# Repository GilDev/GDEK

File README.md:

# GDEK: Your first ergonomic keyboard

Want to try ergonomic keyboards? Don’t know where to start? Don’t want to break the bank yet before knowing what you really want? This may be the keyboard for you.

I created this keyboard following [a little crowdfunding campaign](https://fr.ulule.com/clavier-ergonomique-gildev/) I ran for people that were interested in improving their typing comfort but didn’t want to spend too much money on a device they might not like or would like some feature. This keyboard was entirely designed from scratch, after experimenting for some years with a TypeMatrix 2030, a original X-Bows (Kickstarter edition) and a personnal variant of the Sofle Choc RGB.

## Features

* **4×6 matrix**: you don’t risk missing anything, you can always disable things later on in software to see if missing that top number row would work for you. You can even type in [Bépo](https://bepo.fr/) with minimal modifications!
* **Split**: optimal hands placement, with room in the middle for a trackball or Magic Trackpad, and a simple audio cable to connect the two halves with connectors that won’t mechanically constrain your cable
* **Compact**: despite the “full” matrix, it’s easy to bring it along
* **5 keys thumb cluster**: enough for anything you could imagine
* **Supports MX, Kailh Choc and Gateron KS-33 low-profile switches**: I personnaly use KS-33 switches as they’re low-profile, cheap and support standard MX-compatible keycaps
* **Per-key RGB**: more than just for looks, they can indicate what some keys do, which layer you’re on, etc.
* **Encoder**: you may think it’s a gimmick, but at least you can try it and see if you like it. I love it to scroll, move the cursor, control volume, etc.
* **RP2040**: a very cool and powerful microcontroller that will support any features you could image without breaking a sweat. Easy to flash: it appears like a USB drive that you can drag the firmware onto
* **QMK firmware with VIA support**: easily configurable and customizable via a web app
* **Assembly-friendly**: send the PCB to be assembled and just solder the switches, encoders and audio TRS jack (pretty easy)
* **Open-source**: you can modify the design to your liking, design a case and so on

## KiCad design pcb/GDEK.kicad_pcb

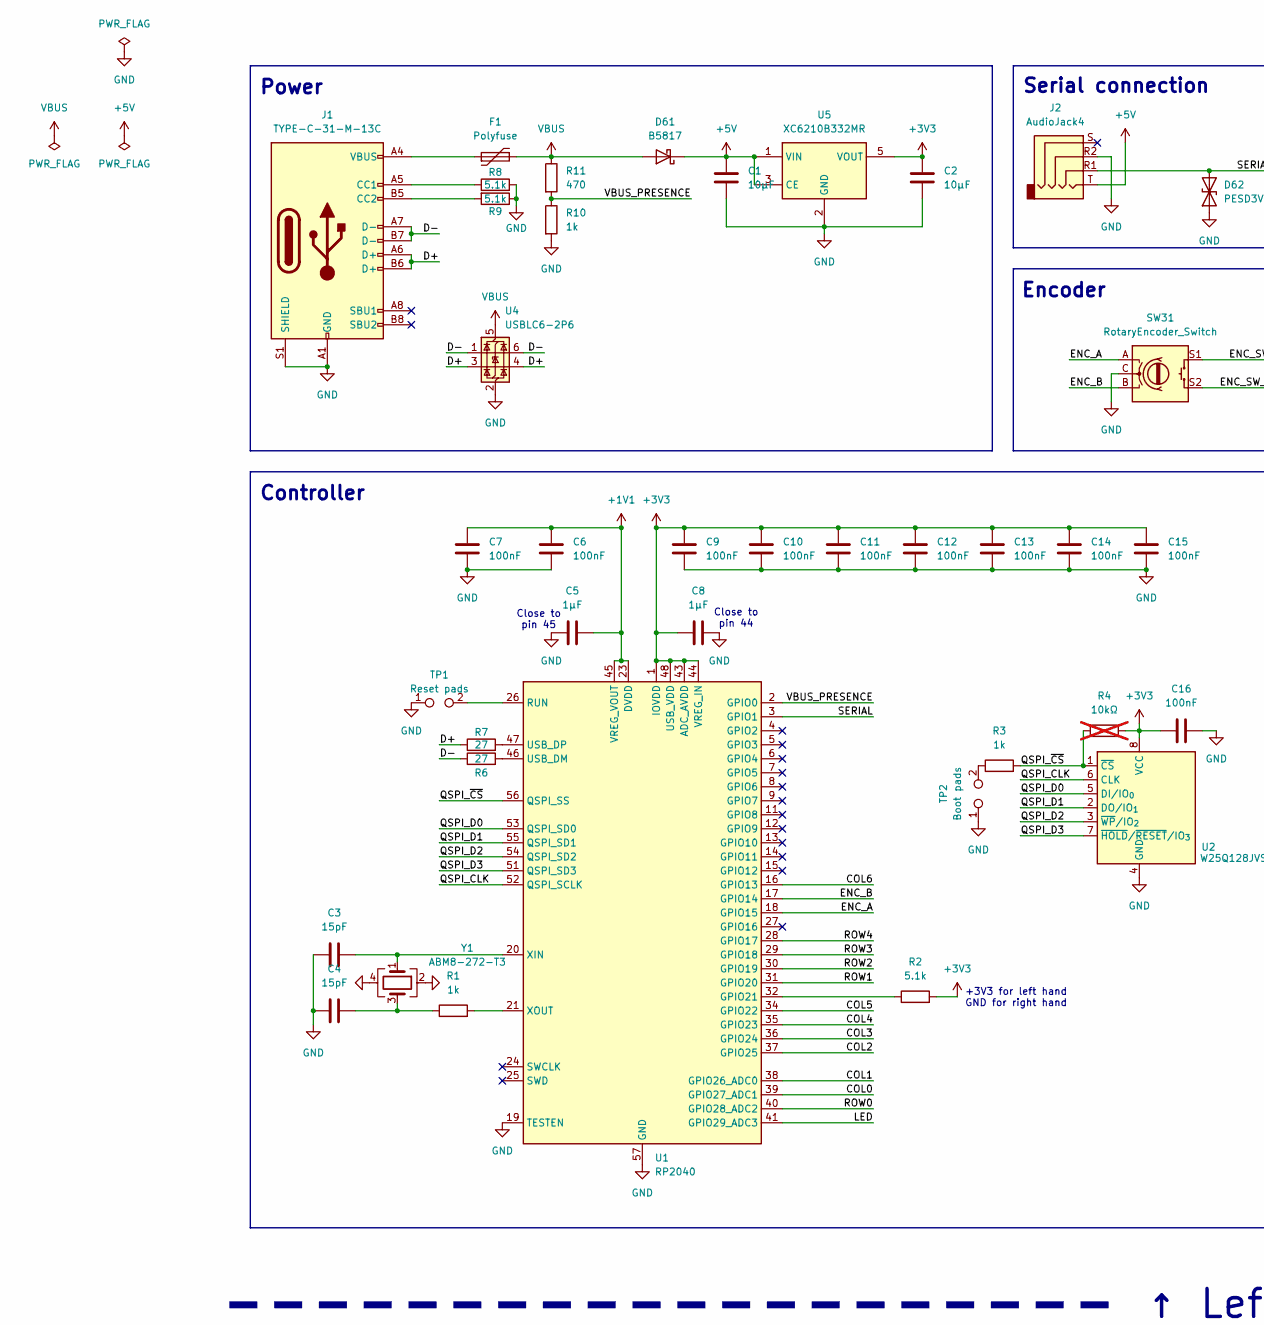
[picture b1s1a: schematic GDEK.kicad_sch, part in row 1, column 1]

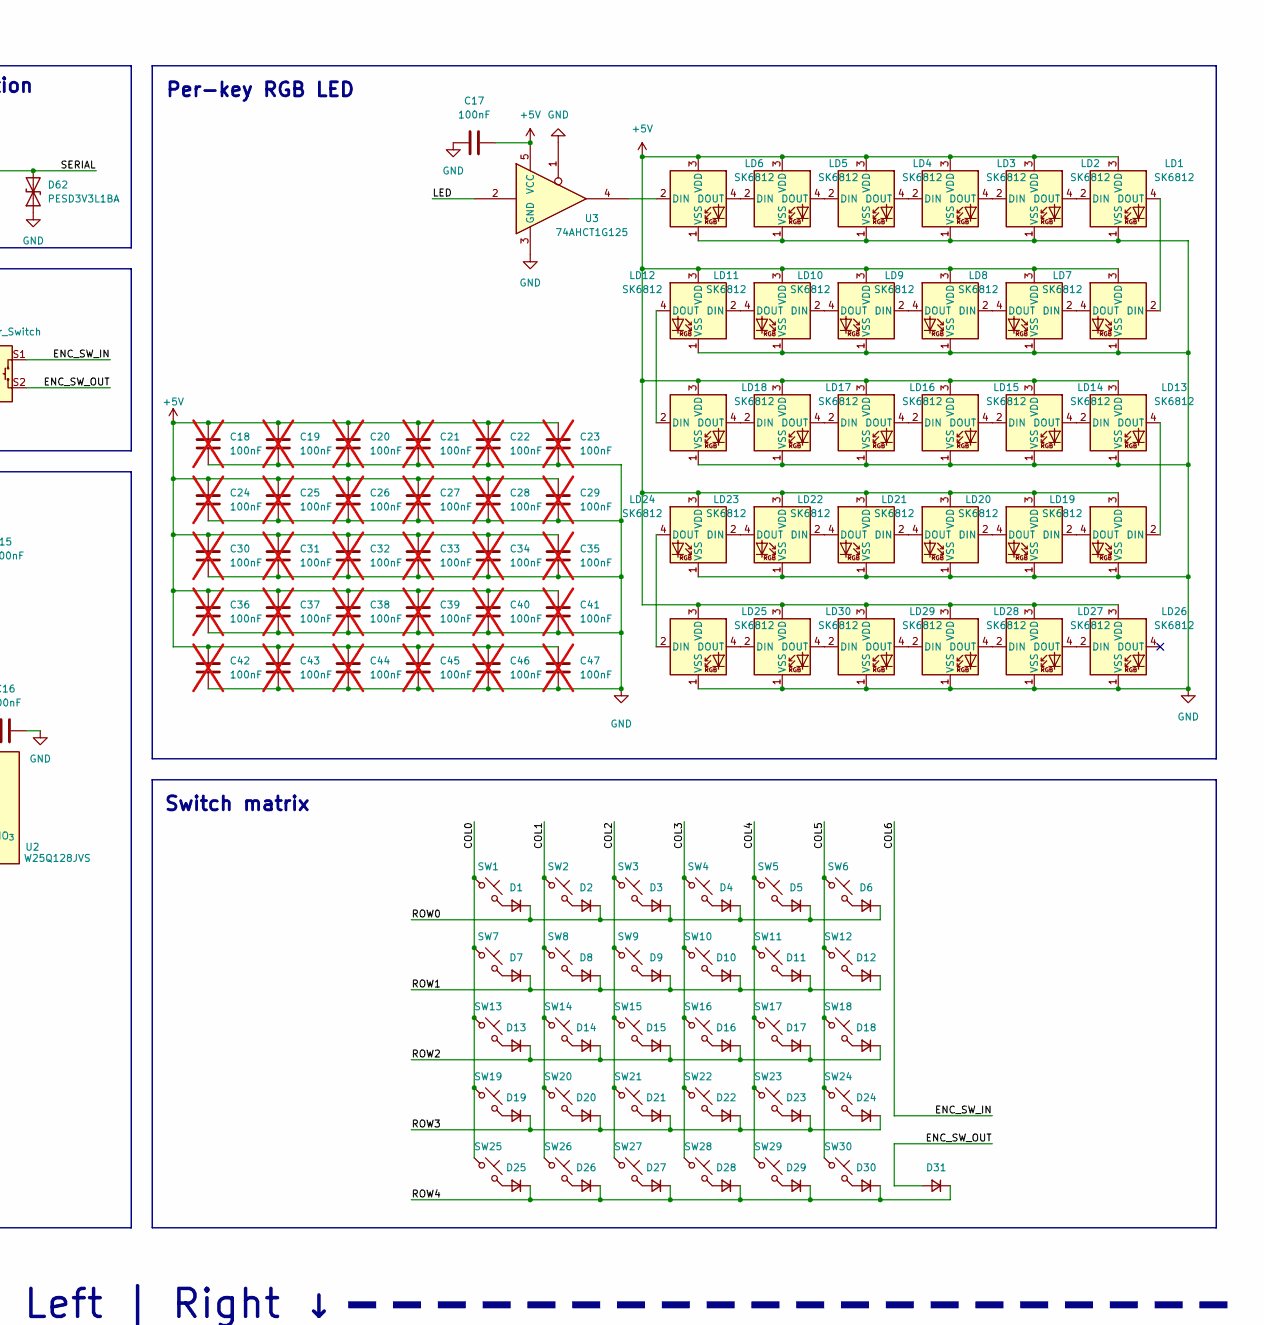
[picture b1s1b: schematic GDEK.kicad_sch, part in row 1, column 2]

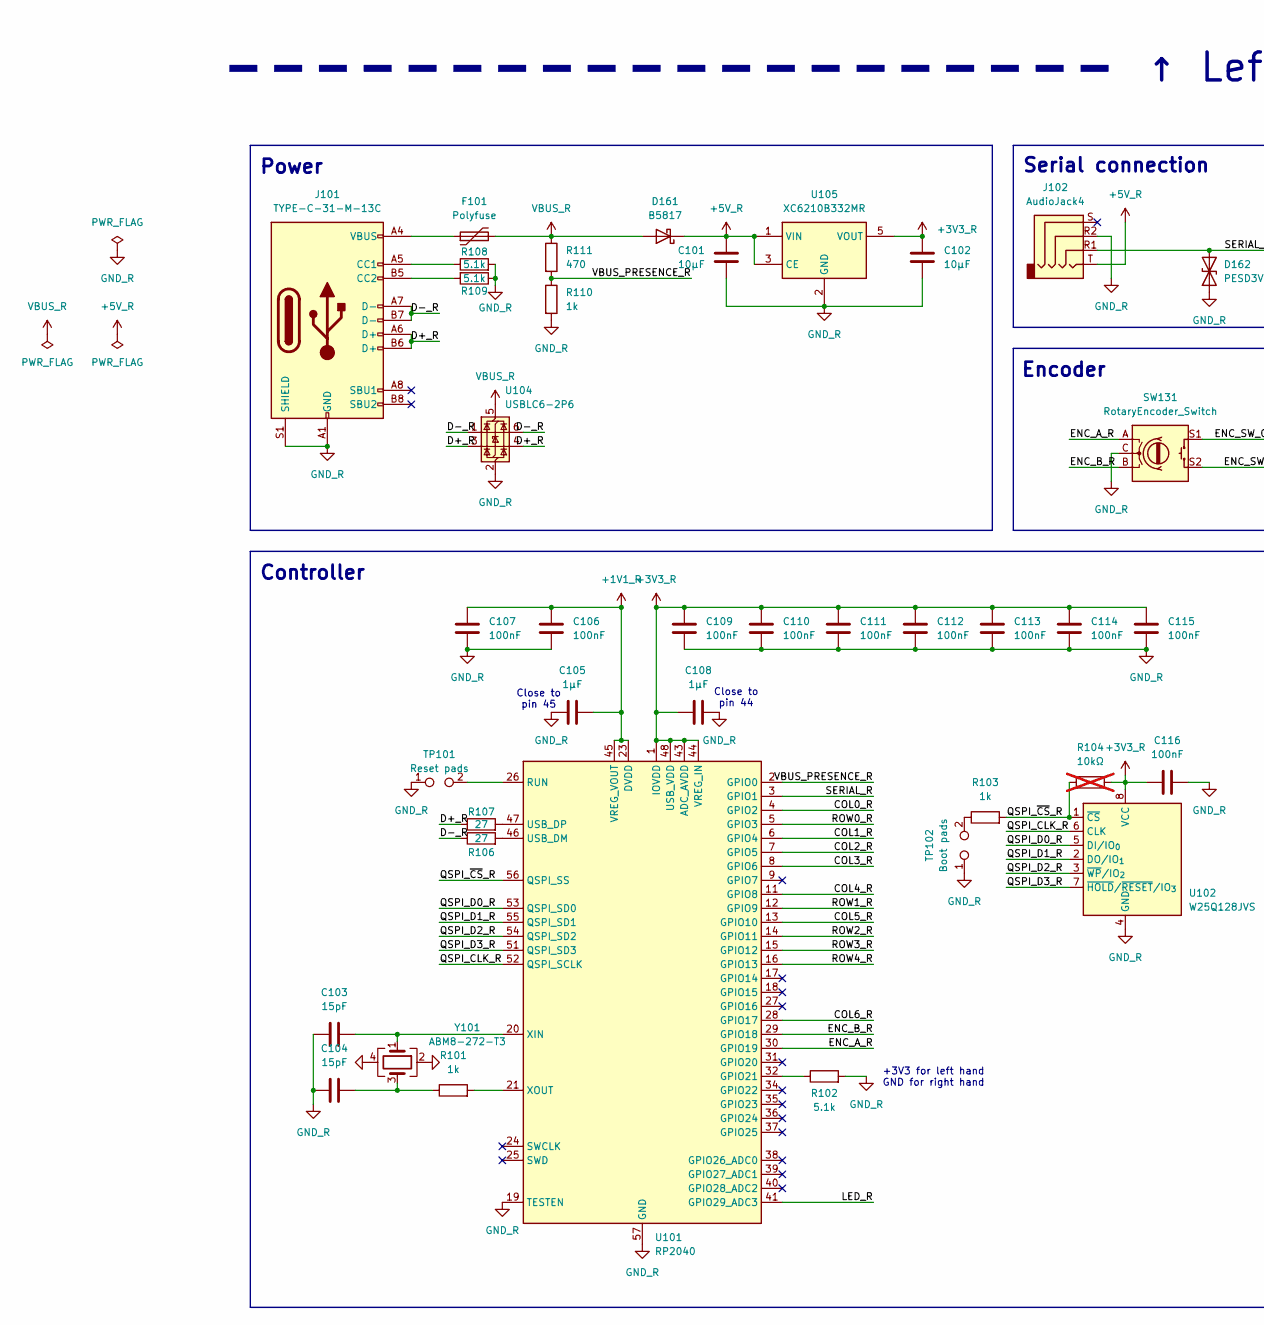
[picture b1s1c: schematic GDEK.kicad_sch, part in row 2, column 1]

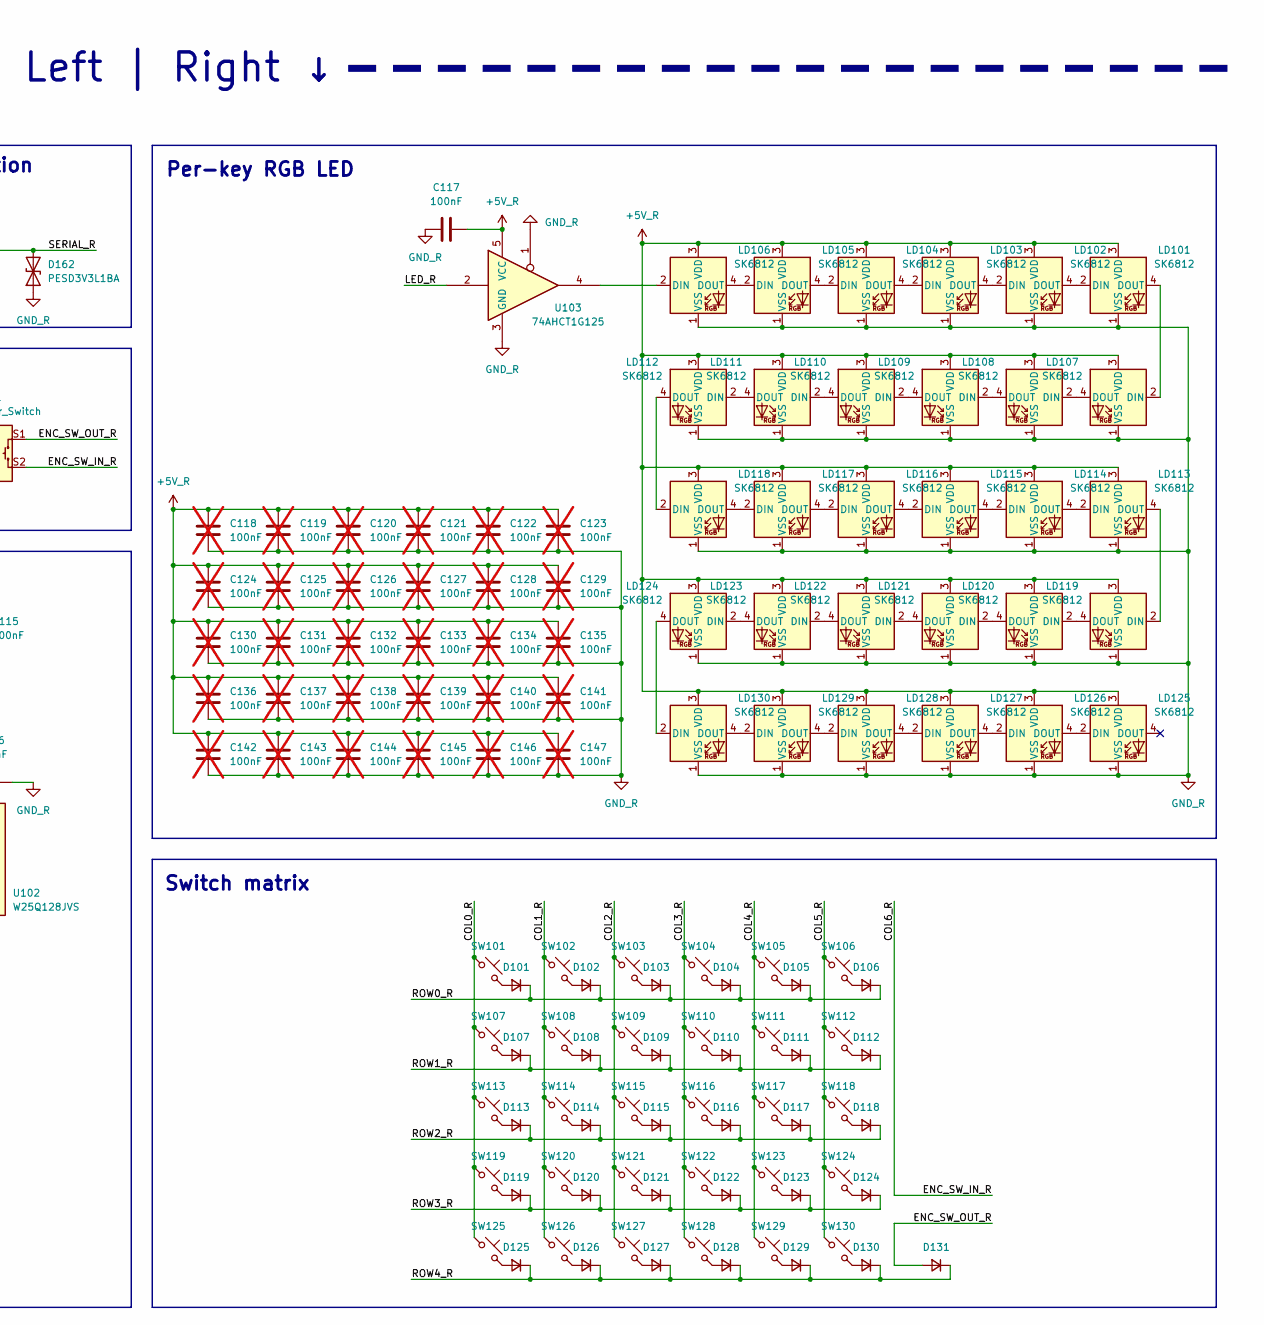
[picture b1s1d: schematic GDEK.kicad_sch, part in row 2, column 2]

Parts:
C1, C2, C101, C102: 10µF; C_0402_1005Metric; LCSC C15525
C3, C4, C103, C104: 15pF; C_0402_1005Metric; LCSC C1548
C5, C8, C105, C108: 1µF; C_0402_1005Metric; LCSC C52923
C6, C7, C9, C10, C11, C12, C13, C14, C15, C16, C17, C106, C107, C109, C110, C111, C112, C113, C114, C115, C116, C117: 100nF; C_0402_1005Metric; LCSC C1525
C18, C19, C20, C21, C22, C23, C24, C25, C26, C27, C28, C29, C30, C31, C32, C33, C34, C35, C36, C37, C38, C39, C40, C41, C42, C43, C44, C45, C46, C47, C118, C119, C120, C121, C122, C123, C124, C125, C126, C127, C128, C129, C130, C131, C132, C133, C134, C135, C136, C137, C138, C139, C140, C141, C142, C143, C144, C145, C146, C147: 100nF; C_0402_1005Metric; LCSC C1525; not fitted
D1, D2, D3, D4, D5, D6, D7, D8, D9, D10, D11, D12, D13, D14, D15, D16, D17, D18, D19, D20, D21, D22, D23, D24, D25, D26, D27, D28, D29, D30, D31, D101, D102, D103, D104, D105, D106, D107, D108, D109, D110, D111, D112, D113, D114, D115, D116, D117, D118, D119, D120, D121, D122, D123, D124, D125, D126, D127, D128, D129, D130, D131: D_Small; D_SOD-123; LCSC C7420318
D61, D161: B5817; D_SOD-323; LCSC C123899
D62, D162: PESD3V3L1BA; D_SOD-323; LCSC C2827682
F1, F101: Polyfuse; Fuse_0603_1608Metric; LCSC C69679
J1, J101: TYPE-C-31-M-13C; USB_C_Receptacle_HRO_TYPE-C-31-M-13B; LCSC C2848620
J2, J102: AudioJack4; AUDIO-TH_PJ-320A-4P-DIP; LCSC C18185602
LD1, LD2, LD3, LD4, LD5, LD6, LD7, LD8, LD9, LD10, LD11, LD12, LD13, LD14, LD15, LD16, LD17, LD18, LD19, LD20, LD21, LD22, LD23, LD24, LD25, LD26, LD27, LD28, LD29, LD30, LD101, LD102, LD103, LD104, LD105, LD106, LD107, LD108, LD109, LD110, LD111, LD112, LD113, LD114, LD115, LD116, LD117, LD118, LD119, LD120, LD121, LD122, LD123, LD124, LD125, LD126, LD127, LD128, LD129, LD130: SK6812; SK6812MINIE; LCSC C5149201
R1, R3, R10, R101, R103, R110: 1k; R_0402_1005Metric; LCSC C11702
R2, R8, R9, R102, R108, R109: 5.1k; R_0402_1005Metric; LCSC C25905
R4, R104: 10kΩ; R_0402_1005Metric; not fitted
R6, R7, R106, R107: 27; R_0402_1005Metric; LCSC C25100
R11, R111: 470; R_0402_1005Metric; LCSC C25117
SW1, SW2, SW3, SW4, SW5, SW6, SW7, SW8, SW9, SW10, SW11, SW12, SW13, SW14, SW15, SW16, SW17, SW18, SW19, SW20, SW21, SW22, SW23, SW24, SW25, SW26, SW27, SW28, SW29, SW30, SW101, SW102, SW103, SW104, SW105, SW106, SW107, SW108, SW109, SW110, SW111, SW112, SW113, SW114, SW115, SW116, SW117, SW118, SW119, SW120, SW121, SW122, SW123, SW124, SW125, SW126, SW127, SW128, SW129, SW130: SW_Push_45deg; MX+KailhChoc+GateronKS_Tight
SW31, SW131: RotaryEncoder_Switch; RotaryEncoder_Alps_EC11E-Switch_Vertical_H20mm
TP1, TP101: Reset pads; SolderJumper-2_P1.3mm_Open_RoundedPad1.0x1.5mm
TP2, TP102: Boot pads; SolderJumper-2_P1.3mm_Open_RoundedPad1.0x1.5mm
U1, U101: RP2040; QFN-56-1EP_7x7mm_P0.4mm_EP3.2x3.2mm; LCSC C2040
U2, U102: W25Q128JVS; SOIC-8_5.3x5.3mm_P1.27mm; LCSC C97521
U3, U103: 74AHCT1G125; SOT-353_SC-70-5; LCSC C151417
U4, U104: USBLC6-2P6; SOT-666; LCSC C2827693
U5, U105: XC6210B332MR; SOT-23-5
Y1, Y101: ABM8-272-T3; Crystal_SMD_3225-4Pin_3.2x2.5mm; LCSC C20625731

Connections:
+1V1: C5.2, C6.1, C7.1, U1.23 (DVDD), U1.45 (VREG_VOUT), U1.50 (DVDD)
+1V1_R: C105.2, C106.1, C107.1, U101.23 (DVDD), U101.45 (VREG_VOUT), U101.50 (DVDD)
+3V3: C2.1, C8.1, C9.1, C10.1, C11.1, C12.1, C13.1, C14.1, C15.1, C16.1, R2.2, R4.2, U1.1 (IOVDD), U1.10 (IOVDD), U1.22 (IOVDD), U1.33 (IOVDD), U1.42 (IOVDD), U1.43 (ADC_AVDD), U1.44 (VREG_IN), U1.48 (USB_VDD), U1.49 (IOVDD), U2.8 (VCC), U5.5 (VOUT)
+3V3_R: C102.1, C108.1, C109.1, C110.1, C111.1, C112.1, C113.1, C114.1, C115.1, C116.1, R104.1, U101.1 (IOVDD), U101.10 (IOVDD), U101.22 (IOVDD), U101.33 (IOVDD), U101.42 (IOVDD), U101.43 (ADC_AVDD), U101.44 (VREG_IN), U101.48 (USB_VDD), U101.49 (IOVDD), U102.8 (VCC), U105.5 (VOUT)
+5V: C1.1, C17.2, C18.2, C19.2, C20.2, C21.2, C22.2, C23.2, C24.2, C25.2, C26.2, C27.2, C28.2, C29.2, C30.2, C31.2, C32.2, C33.2, C34.2, C35.2, C36.2, C37.2, C38.2, C39.2, C40.2, C41.2, C42.2, C43.2, C44.2, C45.2, C46.2, C47.2, D61.1 (K), J2.T, LD1.3 (VDD), LD2.3 (VDD), LD3.3 (VDD), LD4.3 (VDD), LD5.3 (VDD), LD6.3 (VDD), LD7.3 (VDD), LD8.3 (VDD), LD9.3 (VDD), LD10.3 (VDD), LD11.3 (VDD), LD12.3 (VDD), LD13.3 (VDD), LD14.3 (VDD), LD15.3 (VDD), LD16.3 (VDD), LD17.3 (VDD), LD18.3 (VDD), LD19.3 (VDD), LD20.3 (VDD), LD21.3 (VDD), LD22.3 (VDD), LD23.3 (VDD), LD24.3 (VDD), LD25.3 (VDD), LD26.3 (VDD), LD27.3 (VDD), LD28.3 (VDD), LD29.3 (VDD), LD30.3 (VDD), U3.5 (VCC), U5.1 (VIN), U5.3 (CE)
+5V_R: C101.1, C117.2, C118.2, C119.2, C120.2, C121.2, C122.2, C123.2, C124.2, C125.2, C126.2, C127.2, C128.2, C129.2, C130.2, C131.2, C132.2, C133.2, C134.2, C135.2, C136.2, C137.2, C138.2, C139.2, C140.2, C141.2, C142.2, C143.2, C144.2, C145.2, C146.2, C147.2, D161.1 (K), J102.T, LD101.3 (VDD), LD102.3 (VDD), LD103.3 (VDD), LD104.3 (VDD), LD105.3 (VDD), LD106.3 (VDD), LD107.3 (VDD), LD108.3 (VDD), LD109.3 (VDD), LD110.3 (VDD), LD111.3 (VDD), LD112.3 (VDD), LD113.3 (VDD), LD114.3 (VDD), LD115.3 (VDD), LD116.3 (VDD), LD117.3 (VDD), LD118.3 (VDD), LD119.3 (VDD), LD120.3 (VDD), LD121.3 (VDD), LD122.3 (VDD), LD123.3 (VDD), LD124.3 (VDD), LD125.3 (VDD), LD126.3 (VDD), LD127.3 (VDD), LD128.3 (VDD), LD129.3 (VDD), LD130.3 (VDD), U103.5 (VCC), U105.1 (VIN), U105.3 (CE)
/COL0: SW1.1, SW7.1, SW13.1, SW19.1, SW25.1, U1.39 (GPIO27_ADC1)
/COL0_R: SW101.1, SW107.1, SW113.1, SW119.1, SW125.1, U101.4 (GPIO2)
/COL1: SW2.1, SW8.1, SW14.1, SW20.1, SW26.1, U1.38 (GPIO26_ADC0)
/COL1_R: SW102.1, SW108.1, SW114.1, SW120.1, SW126.1, U101.6 (GPIO4)
/COL2: SW3.1, SW9.1, SW15.1, SW21.1, SW27.1, U1.37 (GPIO25)
/COL2_R: SW103.1, SW109.1, SW115.1, SW121.1, SW127.1, U101.7 (GPIO5)
/COL3: SW4.1, SW10.1, SW16.1, SW22.1, SW28.1, U1.36 (GPIO24)
/COL3_R: SW104.1, SW110.1, SW116.1, SW122.1, SW128.1, U101.8 (GPIO6)
/COL4: SW5.1, SW11.1, SW17.1, SW23.1, SW29.1, U1.35 (GPIO23)
/COL4_R: SW105.1, SW111.1, SW117.1, SW123.1, SW129.1, U101.11 (GPIO8)
/COL5: SW6.1, SW12.1, SW18.1, SW24.1, SW30.1, U1.34 (GPIO22)
/COL5_R: SW106.1, SW112.1, SW118.1, SW124.1, SW130.1, U101.13 (GPIO10)
/COL6: SW31.S1, U1.16 (GPIO13)
/COL6_R: SW131.S2, U101.28 (GPIO17)
/D+: J1.A6 (D+), J1.B6 (D+), R7.1, U4.3 (I/O2), U4.4 (I/O2)
/D+_R: J101.A6 (D+), J101.B6 (D+), R107.1, U104.3 (I/O2), U104.4 (I/O2)
/D-: J1.A7 (D-), J1.B7 (D-), R6.1, U4.1 (I/O1), U4.6 (I/O1)
/D-_R: J101.A7 (D-), J101.B7 (D-), R106.1, U104.1 (I/O1), U104.6 (I/O1)
/ENC_A: SW31.A, U1.18 (GPIO15)
/ENC_A_R: SW131.A, U101.30 (GPIO19)
/ENC_B: SW31.B, U1.17 (GPIO14)
/ENC_B_R: SW131.B, U101.29 (GPIO18)
/ENC_SW_OUT: D31.2 (A), SW31.S2
/ENC_SW_OUT_R: D131.2 (A), SW131.S1
/LED: U1.41 (GPIO29_ADC3), U3.2
/LED_R: U101.41 (GPIO29_ADC3), U103.2
/QSPI_CLK: U1.52 (QSPI_SCLK), U2.6 (CLK)
/QSPI_CLK_R: U101.52 (QSPI_SCLK), U102.6 (CLK)
/QSPI_D0: U1.53 (QSPI_SD0), U2.5 (DI/IO_{0})
/QSPI_D0_R: U101.53 (QSPI_SD0), U102.5 (DI/IO_{0})
/QSPI_D1: U1.55 (QSPI_SD1), U2.2 (DO/IO_{1})
/QSPI_D1_R: U101.55 (QSPI_SD1), U102.2 (DO/IO_{1})
/QSPI_D2: U1.54 (QSPI_SD2), U2.3 (~WP/IO_{2})
/QSPI_D2_R: U101.54 (QSPI_SD2), U102.3 (~WP/IO_{2})
/QSPI_D3: U1.51 (QSPI_SD3), U2.7 (~HOLD/~RESET/IO_{3})
/QSPI_D3_R: U101.51 (QSPI_SD3), U102.7 (~HOLD/~RESET/IO_{3})
/QSPI_~CS: R3.2, R4.1, U1.56 (QSPI_SS), U2.1 (~CS)
/QSPI_~CS_R: R103.2, R104.2, U101.56 (QSPI_SS), U102.1 (~CS)
/ROW0: D1.1 (K), D2.1 (K), D3.1 (K), D4.1 (K), D5.1 (K), D6.1 (K), U1.40 (GPIO28_ADC2)
/ROW0_R: D101.1 (K), D102.1 (K), D103.1 (K), D104.1 (K), D105.1 (K), D106.1 (K), U101.5 (GPIO3)
/ROW1: D7.1 (K), D8.1 (K), D9.1 (K), D10.1 (K), D11.1 (K), D12.1 (K), U1.31 (GPIO20)
/ROW1_R: D107.1 (K), D108.1 (K), D109.1 (K), D110.1 (K), D111.1 (K), D112.1 (K), U101.12 (GPIO9)
/ROW2: D13.1 (K), D14.1 (K), D15.1 (K), D16.1 (K), D17.1 (K), D18.1 (K), U1.30 (GPIO19)
/ROW2_R: D113.1 (K), D114.1 (K), D115.1 (K), D116.1 (K), D117.1 (K), D118.1 (K), U101.14 (GPIO11)
/ROW3: D19.1 (K), D20.1 (K), D21.1 (K), D22.1 (K), D23.1 (K), D24.1 (K), U1.29 (GPIO18)
/ROW3_R: D119.1 (K), D120.1 (K), D121.1 (K), D122.1 (K), D123.1 (K), D124.1 (K), U101.15 (GPIO12)
/ROW4: D25.1 (K), D26.1 (K), D27.1 (K), D28.1 (K), D29.1 (K), D30.1 (K), D31.1 (K), U1.28 (GPIO17)
/ROW4_R: D125.1 (K), D126.1 (K), D127.1 (K), D128.1 (K), D129.1 (K), D130.1 (K), D131.1 (K), U101.16 (GPIO13)
/SERIAL: D62.2 (A2), J2.R1, U1.3 (GPIO1)
/SERIAL_R: D162.2 (A2), J102.R1, U101.3 (GPIO1)
/VBUS_PRESENCE: R10.1, R11.2, U1.2 (GPIO0)
/VBUS_PRESENCE_R: R110.1, R111.2, U101.2 (GPIO0)
GND: C1.2, C2.2, C3.1, C4.1, C5.1, C6.2, C7.2, C8.2, C9.2, C10.2, C11.2, C12.2, C13.2, C14.2, C15.2, C16.2, C17.1, C18.1, C19.1, C20.1, C21.1, C22.1, C23.1, C24.1, C25.1, C26.1, C27.1, C28.1, C29.1, C30.1, C31.1, C32.1, C33.1, C34.1, C35.1, C36.1, C37.1, C38.1, C39.1, C40.1, C41.1, C42.1, C43.1, C44.1, C45.1, C46.1, C47.1, D62.1 (A1), J1.A1 (GND), J1.A12 (GND), J1.B1 (GND), J1.B12 (GND), J1.S1 (SHIELD), J2.R2, LD1.1 (VSS), LD2.1 (VSS), LD3.1 (VSS), LD4.1 (VSS), LD5.1 (VSS), LD6.1 (VSS), LD7.1 (VSS), LD8.1 (VSS), LD9.1 (VSS), LD10.1 (VSS), LD11.1 (VSS), LD12.1 (VSS), LD13.1 (VSS), LD14.1 (VSS), LD15.1 (VSS), LD16.1 (VSS), LD17.1 (VSS), LD18.1 (VSS), LD19.1 (VSS), LD20.1 (VSS), LD21.1 (VSS), LD22.1 (VSS), LD23.1 (VSS), LD24.1 (VSS), LD25.1 (VSS), LD26.1 (VSS), LD27.1 (VSS), LD28.1 (VSS), LD29.1 (VSS), LD30.1 (VSS), R8.2, R9.1, R10.2, SW31.C, TP1.1, TP2.1, U1.19 (TESTEN), U1.57 (GND), U2.4 (GND), U3.1, U3.3 (GND), U4.2 (GND), U5.2 (GND), Y1.2, Y1.4; also elsewhere on the board
GND_R: C101.2, C102.2, C103.1, C104.1, C105.1, C106.2, C107.2, C108.2, C109.2, C110.2, C111.2, C112.2, C113.2, C114.2, C115.2, C116.2, C117.1, C118.1, C119.1, C120.1, C121.1, C122.1, C123.1, C124.1, C125.1, C126.1, C127.1, C128.1, C129.1, C130.1, C131.1, C132.1, C133.1, C134.1, C135.1, C136.1, C137.1, C138.1, C139.1, C140.1, C141.1, C142.1, C143.1, C144.1, C145.1, C146.1, C147.1, D162.1 (A1), J101.A1 (GND), J101.A12 (GND), J101.B1 (GND), J101.B12 (GND), J101.S1 (SHIELD), J102.R2, LD101.1 (VSS), LD102.1 (VSS), LD103.1 (VSS), LD104.1 (VSS), LD105.1 (VSS), LD106.1 (VSS), LD107.1 (VSS), LD108.1 (VSS), LD109.1 (VSS), LD110.1 (VSS), LD111.1 (VSS), LD112.1 (VSS), LD113.1 (VSS), LD114.1 (VSS), LD115.1 (VSS), LD116.1 (VSS), LD117.1 (VSS), LD118.1 (VSS), LD119.1 (VSS), LD120.1 (VSS), LD121.1 (VSS), LD122.1 (VSS), LD123.1 (VSS), LD124.1 (VSS), LD125.1 (VSS), LD126.1 (VSS), LD127.1 (VSS), LD128.1 (VSS), LD129.1 (VSS), LD130.1 (VSS), R102.2, R108.2, R109.1, R110.2, SW131.C, TP101.1, TP102.1, U101.19 (TESTEN), U101.57 (GND), U102.4 (GND), U103.1, U103.3 (GND), U104.2 (GND), U105.2 (GND), Y101.2, Y101.4; also elsewhere on the board
unnamed: C4.2, R1.1, Y1.3
unnamed: C104.2, R101.1, Y101.3
unnamed: D1.2 (A), SW1.2
unnamed: D2.2 (A), SW2.2
unnamed: D3.2 (A), SW3.2
unnamed: D4.2 (A), SW4.2
unnamed: D5.2 (A), SW5.2
unnamed: D6.2 (A), SW6.2
unnamed: D7.2 (A), SW7.2
unnamed: D8.2 (A), SW8.2
unnamed: D9.2 (A), SW9.2
unnamed: D10.2 (A), SW10.2
unnamed: D11.2 (A), SW11.2
unnamed: D12.2 (A), SW12.2
unnamed: D13.2 (A), SW13.2
unnamed: D14.2 (A), SW14.2
unnamed: D15.2 (A), SW15.2
unnamed: D16.2 (A), SW16.2
unnamed: D17.2 (A), SW17.2
unnamed: D18.2 (A), SW18.2
unnamed: D19.2 (A), SW19.2
unnamed: D20.2 (A), SW20.2
unnamed: D21.2 (A), SW21.2
unnamed: D22.2 (A), SW22.2
unnamed: D23.2 (A), SW23.2
unnamed: D24.2 (A), SW24.2
unnamed: D25.2 (A), SW25.2
unnamed: D26.2 (A), SW26.2
unnamed: D27.2 (A), SW27.2
unnamed: D28.2 (A), SW28.2
unnamed: D29.2 (A), SW29.2
unnamed: D30.2 (A), SW30.2
unnamed: D101.2 (A), SW101.2
unnamed: D102.2 (A), SW102.2
unnamed: D103.2 (A), SW103.2
unnamed: D104.2 (A), SW104.2
unnamed: D105.2 (A), SW105.2
unnamed: D106.2 (A), SW106.2
unnamed: D107.2 (A), SW107.2
unnamed: D108.2 (A), SW108.2
unnamed: D109.2 (A), SW109.2
unnamed: D110.2 (A), SW110.2
unnamed: D111.2 (A), SW111.2
unnamed: D112.2 (A), SW112.2
unnamed: D113.2 (A), SW113.2
unnamed: D114.2 (A), SW114.2
unnamed: D115.2 (A), SW115.2
unnamed: D116.2 (A), SW116.2
unnamed: D117.2 (A), SW117.2
unnamed: D118.2 (A), SW118.2
unnamed: D119.2 (A), SW119.2
unnamed: D120.2 (A), SW120.2
unnamed: D121.2 (A), SW121.2
unnamed: D122.2 (A), SW122.2
unnamed: D123.2 (A), SW123.2
unnamed: D124.2 (A), SW124.2
unnamed: D125.2 (A), SW125.2
unnamed: D126.2 (A), SW126.2
unnamed: D127.2 (A), SW127.2
unnamed: D128.2 (A), SW128.2
unnamed: D129.2 (A), SW129.2
unnamed: D130.2 (A), SW130.2
unnamed: F1.1, J1.A4 (VBUS), J1.A9 (VBUS), J1.B4 (VBUS), J1.B9 (VBUS)
unnamed: F101.1, J101.A4 (VBUS), J101.A9 (VBUS), J101.B4 (VBUS), J101.B9 (VBUS)
unnamed: J1.A5 (CC1), R8.1
unnamed: J1.B5 (CC2), R9.2
unnamed: J101.A5 (CC1), R108.1
unnamed: J101.B5 (CC2), R109.2
unnamed: LD1.2 (DIN), LD2.4 (DOUT)
unnamed: LD1.4 (DOUT), LD7.2 (DIN)
unnamed: LD2.2 (DIN), LD3.4 (DOUT)
unnamed: LD3.2 (DIN), LD4.4 (DOUT)
unnamed: LD4.2 (DIN), LD5.4 (DOUT)
unnamed: LD5.2 (DIN), LD6.4 (DOUT)
unnamed: LD6.2 (DIN), U3.4
unnamed: LD7.4 (DOUT), LD8.2 (DIN)
unnamed: LD8.4 (DOUT), LD9.2 (DIN)
unnamed: LD9.4 (DOUT), LD10.2 (DIN)
unnamed: LD10.4 (DOUT), LD11.2 (DIN)
unnamed: LD11.4 (DOUT), LD12.2 (DIN)
unnamed: LD12.4 (DOUT), LD18.2 (DIN)
unnamed: LD13.2 (DIN), LD14.4 (DOUT)
unnamed: LD13.4 (DOUT), LD19.2 (DIN)
unnamed: LD14.2 (DIN), LD15.4 (DOUT)
unnamed: LD15.2 (DIN), LD16.4 (DOUT)
unnamed: LD16.2 (DIN), LD17.4 (DOUT)
unnamed: LD17.2 (DIN), LD18.4 (DOUT)
unnamed: LD19.4 (DOUT), LD20.2 (DIN)
unnamed: LD20.4 (DOUT), LD21.2 (DIN)
unnamed: LD21.4 (DOUT), LD22.2 (DIN)
unnamed: LD22.4 (DOUT), LD23.2 (DIN)
unnamed: LD23.4 (DOUT), LD24.2 (DIN)
unnamed: LD24.4 (DOUT), LD25.2 (DIN)
unnamed: LD25.4 (DOUT), LD30.2 (DIN)
unnamed: LD26.2 (DIN), LD27.4 (DOUT)
unnamed: LD27.2 (DIN), LD28.4 (DOUT)
unnamed: LD28.2 (DIN), LD29.4 (DOUT)
unnamed: LD29.2 (DIN), LD30.4 (DOUT)
unnamed: LD101.2 (DIN), LD102.4 (DOUT)
unnamed: LD101.4 (DOUT), LD107.2 (DIN)
unnamed: LD102.2 (DIN), LD103.4 (DOUT)
unnamed: LD103.2 (DIN), LD104.4 (DOUT)
unnamed: LD104.2 (DIN), LD105.4 (DOUT)
unnamed: LD105.2 (DIN), LD106.4 (DOUT)
unnamed: LD106.2 (DIN), U103.4
unnamed: LD107.4 (DOUT), LD108.2 (DIN)
unnamed: LD108.4 (DOUT), LD109.2 (DIN)
unnamed: LD109.4 (DOUT), LD110.2 (DIN)
unnamed: LD110.4 (DOUT), LD111.2 (DIN)
unnamed: LD111.4 (DOUT), LD112.2 (DIN)
unnamed: LD112.4 (DOUT), LD118.2 (DIN)
unnamed: LD113.2 (DIN), LD114.4 (DOUT)
unnamed: LD113.4 (DOUT), LD119.2 (DIN)
unnamed: LD114.2 (DIN), LD115.4 (DOUT)
unnamed: LD115.2 (DIN), LD116.4 (DOUT)
unnamed: LD116.2 (DIN), LD117.4 (DOUT)
unnamed: LD117.2 (DIN), LD118.4 (DOUT)
unnamed: LD119.4 (DOUT), LD120.2 (DIN)
unnamed: LD120.4 (DOUT), LD121.2 (DIN)
unnamed: LD121.4 (DOUT), LD122.2 (DIN)
unnamed: LD122.4 (DOUT), LD123.2 (DIN)
unnamed: LD123.4 (DOUT), LD124.2 (DIN)
unnamed: LD124.4 (DOUT), LD130.2 (DIN)
unnamed: LD125.2 (DIN), LD126.4 (DOUT)
unnamed: LD126.2 (DIN), LD127.4 (DOUT)
unnamed: LD127.2 (DIN), LD128.4 (DOUT)
unnamed: LD128.2 (DIN), LD129.4 (DOUT)
unnamed: LD129.2 (DIN), LD130.4 (DOUT)
unnamed 188: R3.1, TP2.2; also elsewhere on the board
unnamed 189: R103.1, TP102.2; also elsewhere on the board
unnamed: R2.1, U1.32 (GPIO21)
unnamed 191: TP1.2, U1.26 (RUN); also elsewhere on the board
unnamed: R6.2, U1.46 (USB_DM)
unnamed: R7.2, U1.47 (USB_DP)
unnamed: C3.2, U1.20 (XIN), Y1.1
unnamed: R1.2, U1.21 (XOUT)
unnamed: R102.1, U101.32 (GPIO21)
unnamed 197: TP101.2, U101.26 (RUN); also elsewhere on the board
unnamed: R106.2, U101.46 (USB_DM)
unnamed: R107.2, U101.47 (USB_DP)
unnamed: C103.2, U101.20 (XIN), Y101.1
unnamed: R101.2, U101.21 (XOUT)
VBUS: D61.2 (A), F1.2, R11.1, U4.5 (VBUS)
VBUS_R: D161.2 (A), F101.2, R111.1, U104.5 (VBUS)

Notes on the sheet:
Close to pin 44
Power
+3V3 for left hand GND for right hand
Per-key RGB LED
Switch matrix
Serial connection
Close to pin 45
Controller
Encoder
↑ Left | Right ↓

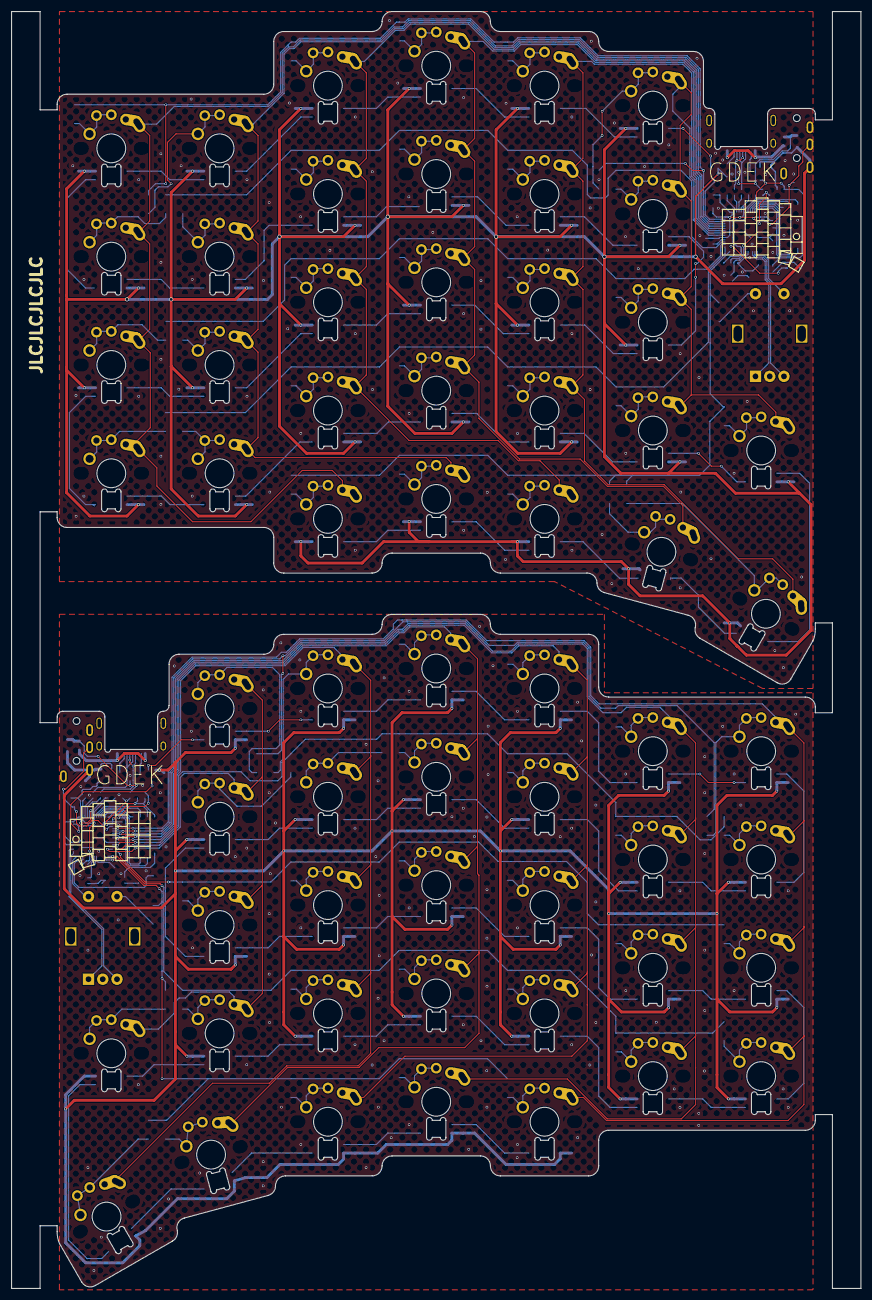
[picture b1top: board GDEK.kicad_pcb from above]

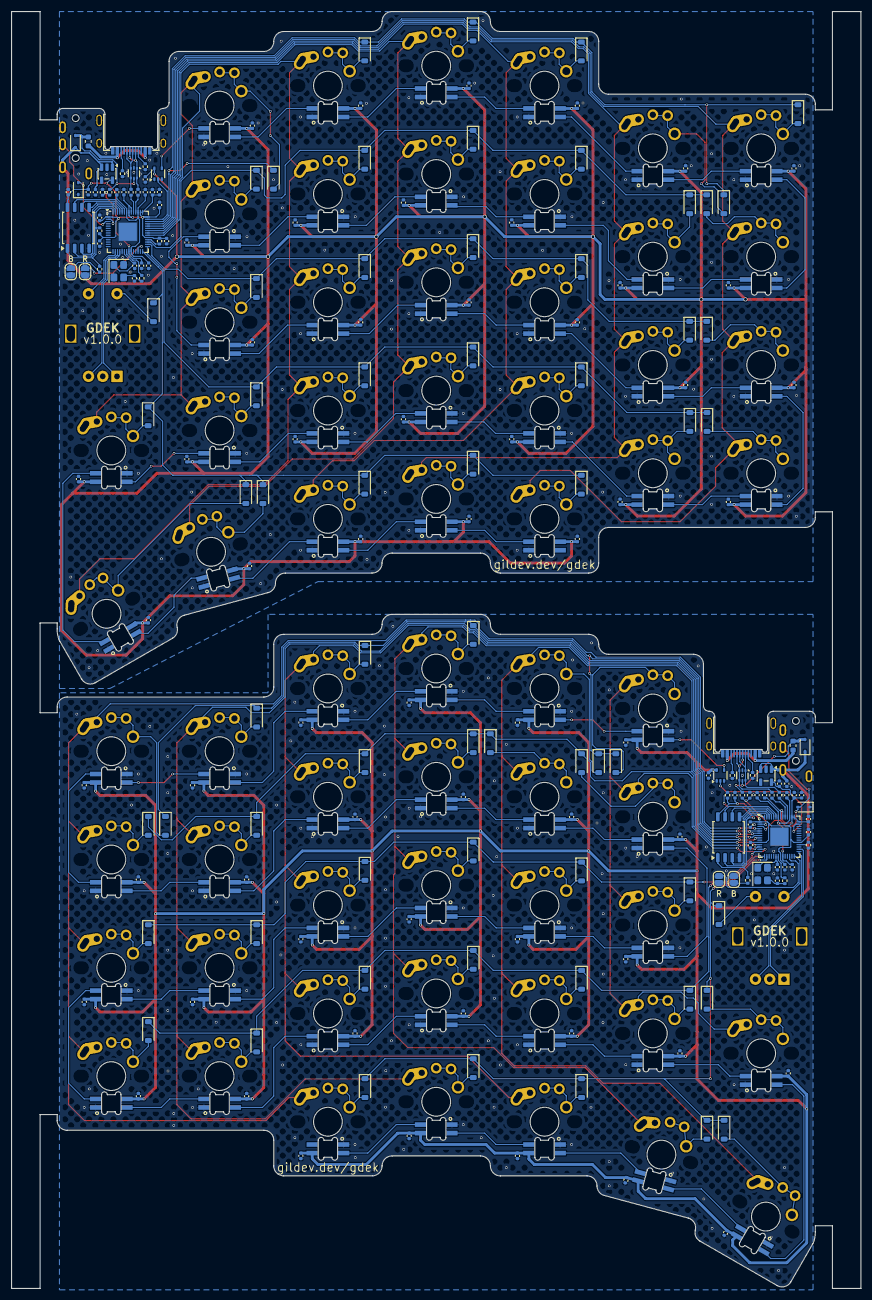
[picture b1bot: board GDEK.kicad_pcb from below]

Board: 2 copper layers, 149.0 x 224.0 mm, 324 parts (260 on the bottom side), 204 nets.

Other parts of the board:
B: Boot pads; SolderJumper-2_P1.3mm_Open_RoundedPad1.0x1.5mm
B#2: Boot pads; SolderJumper-2_P1.3mm_Open_RoundedPad1.0x1.5mm
R: Reset pads; SolderJumper-2_P1.3mm_Open_RoundedPad1.0x1.5mm
R#2: Reset pads; SolderJumper-2_P1.3mm_Open_RoundedPad1.0x1.5mm

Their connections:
GND: B.1, R.1; also elsewhere on the board
GND_R: B#2.1, R#2.1; also elsewhere on the board
unnamed 188: B.2; also elsewhere on the board
unnamed 189: B#2.2; also elsewhere on the board
unnamed 191: R.2; also elsewhere on the board
unnamed 197: R#2.2; also elsewhere on the board

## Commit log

2025-02-08 🎉 Initial commit
2025-02-09 ♻️ Make switch symbol multi-unit for switch and LED
    Also changes VBUS_PRESENCE voltage divider’s resistors and handedness pull-up/down resistor in order to remove one reference (10kΩ).
2025-02-09 🔧 Finish footprint assignments
2025-02-10 ✨ Finish left hand PCB
2025-02-10 📝 Add 3D renders to README
2025-02-16 ✨ Add optional decoupling for each LED
2025-03-16 ♻️ Split and improve switch and LED footprints
    Tighter tolerances and split so that PCBA isn’t getting confused by the footprint having both components on top (switch) and bottom (LED).
2025-03-16 ♻️ Replace LED and reroute them
    They are flipped on odd rows to have a better layout not requiring any layer switch because of the new LED footprint with mouse ears.
2025-04-02 ✨ Update lots of stuff (and make the thumb cluster round)
2025-04-02 ✨ Finish board outline
    Fix thumb cluster’s rounded corners. Add rounded corners near connectors. Add milled slots for USB-C connector’s corners.
2025-04-05 ✨ Route LED power and decoupling
2025-04-05 🚧 Start moving components and traces near USB connector
2025-04-05 ⏪️ Put the USB connector back down (recessed)
    Because most cables used with the keyboard will be straights (and not right angled), I prefer to just recess the connector and keep 2 mm margin on each side for the male connector to fit in. That mak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
2025-04-06 🔧 Refine board constraints and components positions
    I think this time is the one! The encoder will be able to accept 20 mm knobs which I feel are better to use.
2025-04-06 🐛 Fix matrix traces
    Had to be moved because of the outline change on the top right switch.
2025-04-13 ✨ Route LED power rails
2025-04-13 🚨 Fix all DRC issues!
    For real! Still have to check clearance to board outline later on, mostly for the jack connector’s pads.
    Other half can probably be started now! Or maybe I try to make this one reversible, that would be cool, but required two-sides assembly because of the LEDs.
    This evening was pretty productive, good night!
2025-04-14 ✨ Add tooling holes for assembly
2025-04-14 ✨ Add hatch pattern on planes
2025-04-14 🎨 Clean up planes
2025-04-14 ➕ Add missing encoder footprint
    Hide silkscreen.
2025-04-14 ✨ Add order number on PCB (hidden)
2025-04-16 🚧 V-cut panelization test
    Change the shape of the board to have two straight edges, allowing to add tooling rails required for PCB assembly. This removes some PCB under the thumb’s outermost key. The whole board could also be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
2025-04-16 ✨ Start right hand (outline and switch placement done)
2025-04-16 ✨ Right hand: place encoder and connectors
2025-04-16 🚧 Place LEDs
2025-04-17 ✨ Right hand: place diodes
2025-04-17 ✨ Right hand: finish LEDs positioning
2025-04-17 ✨ Right hand: place decoupling capacitors of LEDs
2025-04-19 🎨 Set all capacitors in the same orientation
    There was one remaining horizontal one.
2025-04-19 🎨 Remove component references from silkscreen
    YOLO.
2025-04-20 ⚰️ Remove debug pins
    YOLO.
2025-04-21 ✨ Route right hand (except encoder)
    Getting late! Will hopefully finish tomorrow. Then DRC, then panelization with vcuts, then order!
2025-04-21 ✨ Finish routing of right hand!
    Finally! No DRC error!
2025-04-21 ♻️ Change board outline for v-cut panelization
2025-04-23 ✨ Add tooling rails
    Required for a PCBA of a big number of board.
2025-04-23 ⚡️ Improve ground planes fill
2025-04-23 ✨ Add v-cuts on User.1 layer
2025-04-23 🎨 Mode order number to tooling edge
2025-04-25 ✨ Mirror silkscreen
2025-04-25 🎨 Add encoder 3D model
    First embedded model, that’s cool!
2025-04-25 🔧 Adjust copper to board edge clearance
    It’s not perfect, it’s 0.05 mm but the v-cut edges have a 0.4 mm clearance in order to avoid having teared copper planes. Can’t do much more it seems otherwise the Type-C port and LED pads are quite 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
2025-04-25 🎨 Move vias out of silkscreen as much as possible
2025-04-25 ⚡️ Update fiducials and vias
2025-04-27 ⚡️ Improve vias placement
2025-04-27 🔖 Bump version to v1.0.0
2025-04-27 🐛 Fix BOM
    Type-C footprint was wrong on right half.
2025-04-29 🚧 Flip right hand
    Unfinished, but can reduce panel’s length by ~15 mm. Yeah I didn’t think through this enough, oh well…
2025-04-29 ⚡️ Flip right hand
    Reduces panel length by ~15 mm. 149×224 mm total.
2025-04-29 📦️ Add missing 3D model of LED
2025-09-24 🔥 Remove protection resistor on serial line
    This prevents communication between halves because of the high impedance of the MCU’s GPIO which makes a low level at a voltage too high to be registered as low.
2025-09-24 🔧 Make switches center holes a tad bigger
    Two cents bigger. Hopefully the switches are still properly maintained but without having to force too much to insert them all at the same time (using my little soldering tool).
2025-09-24 🎨 Hide traces under inner thumb key and improve ground planes
2025-09-29 ✨ Rearrange some diodes on the right hand
    So that silicone feet can be installed as close to the edge as possible.
2025-09-29 ✨ Rearrange some diodes on the left hand
    So that silicone feet can be installed as close to the edge as possible.
2025-09-30 ♻️ Put the encoders’ switches on the matrix
    Required if I want to be able to remap it using VIA or Vial. Yeah it’s a bummer…
    Also fixed all DRC issues (updated standard footprints and reduced courtyard’s size of SK6812MINI-E because of the slightly bigger switches’ holes).
2025-10-01 🔧 Make LED hole a tad smaller
    The part between this hole and the switch’s hole is already pretty thin, making the switch’s hole bigger makes it even thinner, so I reduced the hole’s height by two cents (going from ~0.27 mm to ~0.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
    Also adjusted a few vias and ran DRC again.
2025-10-01 🔧 Move some diodes a bit
2025-10-17 ⬆️ Update standard footprints
2025-10-22 🔧 Make LED hole a tad smaller
    Manufacturing files didn’t change so I made the hole 0.05 mm bigger instead of 0.02 mm bigger, hopefully that is somehow reflected in the output files but I’m not entirely sure…
    It was 5 mm at first, now 5.05. I think 5.1 would be too big, it just fits right now, but the JLCPCB tolerances are apparently 0.2 mm so maybe I got lucky on the first two prototype batches…
